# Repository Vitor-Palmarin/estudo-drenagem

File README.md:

# Automação de bancada experimental para determinação de percolação de água em minério de ferro

O grande fluxo de mercadorias ao redor do mundo é algo vital para a economia mundial, e com isso se faz necessário um transporte que possibilite uma grande movimentação de carga e com um bom custo-benefício. As malhas ferroviárias são uma ótima opção para fazer o transporte de cargas de grande porte, como grãos, minérios, entre outros, permitindo assim, uma conexão direta entre vários pontos de produção, desde a extração da obra-prima até a exportação do produto nos portos. O transporte de minérios é feito em vagões abertos, causando um acúmulo de água desnecessária sobre o material em épocas de chuva, e a fim de solucionar essa problemática, está sendo estudado o uso de drenos para fazer o escoamento de água livre. O uso de drenos para fazer o escoamento de água livre sofre constantes entupimentos, necessitando de paradas no transporte onerosas para sua desobstrução. 
Foi desenvolvido um protótipo de bancada experimental para o estudo do sistema de drenagem em amostras do minério de ferro do tipo Sinter feed com diferentes concentrações mássicas, utilizando uma bancada experimental desenvolvida com drenos confeccionados em ABS por uma impressora 3D. 

A automação da bancada utilizou um microcontrolador ATmega, que por meio de sensores de ultrassom foi medida a altura do fluído e armazenada os resultados da medição em um arquivo de extensão CSV por meio de um cartão Micro SD, durante um intervalo definido previamente definido, com exibição da coleta em tempo real em um display LCD.

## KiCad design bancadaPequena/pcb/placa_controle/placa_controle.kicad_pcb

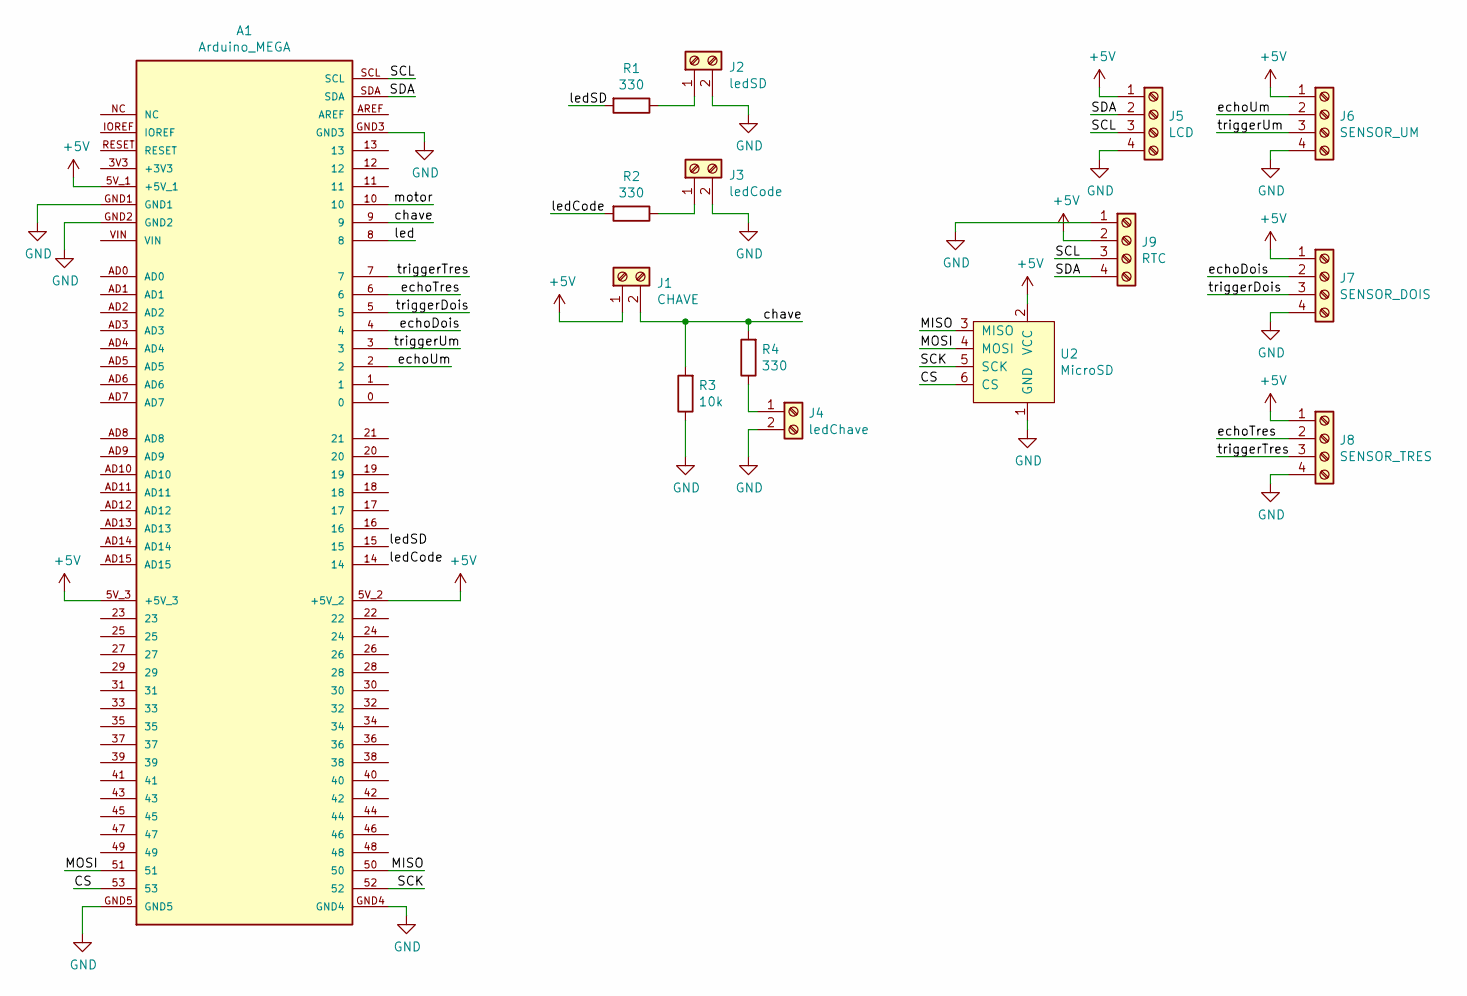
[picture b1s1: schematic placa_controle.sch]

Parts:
A1: Arduino_MEGA
J1: CHAVE; Altech_AK300_1x02_P5.00mm_45-Degree
J2: ledSD; PinSocket_1x02_P2.54mm_Vertical
J3: ledCode; PinSocket_1x02_P2.54mm_Vertical
J4: ledChave; PinSocket_1x02_P2.54mm_Vertical
J5: LCD; Altech_AK300_1x04_P5.00mm_45-Degree
J6: SENSOR_UM; Altech_AK300_1x04_P5.00mm_45-Degree
J7: SENSOR_DOIS; Altech_AK300_1x04_P5.00mm_45-Degree
J8: SENSOR_TRES; Altech_AK300_1x04_P5.00mm_45-Degree
J9: RTC; PinSocket_1x04_P2.54mm_Vertical
R1, R2, R4: 330; R_Axial_DIN0207_L6.3mm_D2.5mm_P10.16mm_Horizontal
R3: 10k; R_Axial_DIN0207_L6.3mm_D2.5mm_P10.16mm_Horizontal
U2: MicroSD; PinSocket_1x06_P2.54mm_Vertical

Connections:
+5V: A1.5V_1 (+5V_1), A1.5V_2 (+5V_2), A1.5V_3 (+5V_3), J1.1, J5.1, J6.1, J7.1, J8.1, J9.2, U2.2 (VCC)
/CS: A1.53, U2.6 (CS)
/MISO: A1.50, U2.3 (MISO)
/MOSI: A1.51, U2.4 (MOSI)
/SCK: A1.52, U2.5 (SCK)
/SCL: A1.SCL, J5.3, J9.3
/SDA: A1.SDA, J5.2, J9.4
/chave: A1.9, J1.2, R3.2, R4.2
/echoDois: A1.4, J7.2
/echoTres: A1.6, J8.2
/echoUm: A1.2, J6.2
/led: A1.8
/ledCode: A1.14, R2.2
/ledSD: A1.15, R1.2
/motor: A1.10
/triggerDois: A1.5, J7.3
/triggerTres: A1.7, J8.3
/triggerUm: A1.3, J6.3
GND: A1.GND1, A1.GND2, A1.GND3, A1.GND4, A1.GND5, J2.2, J3.2, J4.2, J5.4, J6.4, J7.4, J8.4, J9.1, R3.1, U2.1 (GND)
unnamed: J2.1, R1.1
unnamed: J3.1, R2.1
unnamed: J4.1, R4.1

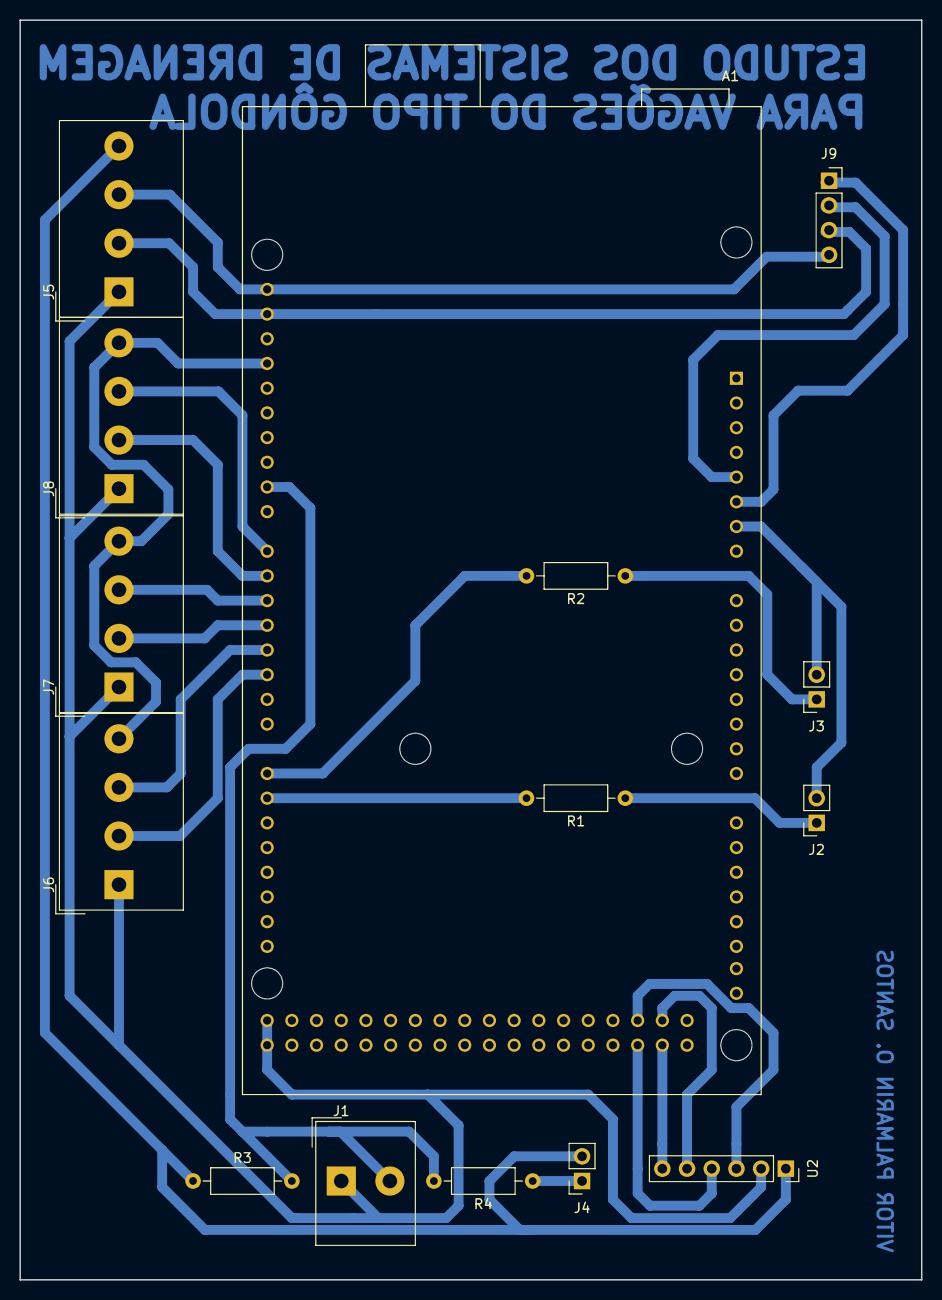
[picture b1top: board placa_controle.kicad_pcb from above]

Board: 2 copper layers, 92.7 x 129.5 mm, 15 parts (0 on the bottom side), 20 nets.

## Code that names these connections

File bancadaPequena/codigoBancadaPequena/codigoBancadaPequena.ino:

/* BANCADA EXPERIMENTAL PARA ESTUDO DOS SISTEMAS DE DRENAGEM PARA VAGÕES DE CARGA TIPO GÔNDOLA
 * 
 * DESENVOLVIDO POR: VITOR PALMARIN OLIVEIRA SANTOS - 10/2021
 * 
 */
// === DECLARACAO DE BIBLIOTECAS ===
#include <SPI.h>
#include <SD.h>
#include <Wire.h>;
#include <LiquidCrystal_I2C.h>;

// === DECLARAÇÃO DE OBJETOS ===
LiquidCrystal_I2C lcd(0x27, 20, 4);

// === PINAGEM ===
const int chipSelect = 10;

const int triggerUm = 2;
const int echoUm = 3;

const int triggerDois = 4;
const int echoDois = 5;

const int triggerTres = 6;
const int echoTres = 7;

const int led = 9;

const int chave = 8;

// === VARIAVEIS ===
long intervaloColeta = millis();
long intervaloLed = millis();
long intervaloExibicao = millis();

long pulsoUm, 
     pulsoDois, 
     pulsoTres;

int nivelUm, 
    nivelDois, 
    nivelTres;

const int alturaTanque = 506; // altura do tanque em milimetros

bool opcao = 0;

void setup()
{
  Serial.begin(9600);
  lcd.init();
  lcd.backlight();

  pinMode(triggerUm, OUTPUT);
  pinMode(echoUm, INPUT); 
  pinMode(triggerDois, OUTPUT);
  pinMode(echoDois, INPUT);
  pinMode(triggerTres, OUTPUT);
  pinMode(echoTres, INPUT);
  pinMode(led, OUTPUT);
  pinMode(chave, INPUT);

  digitalWrite(triggerUm, LOW);
  digitalWrite(triggerDois, LOW);
  digitalWrite(triggerTres, LOW);
  digitalWrite(led, LOW);
  
  Serial.println("Inicializando cartao SD...");
  if (!SD.begin(chipSelect))
  {
    Serial.println("Falha ao acessar o cartao !");
    Serial.println("Verifique o cartao/conexoes e reinicie o Arduino...");
    return;
  }
  Serial.println("Cartao iniciado corretamente !\n");
}

void loop()
{
  if((millis() - intervaloLed) >= 500){    // pisca o led no intervalo de 0,5 segundo
    intervaloLed = millis();
    digitalWrite(led,!digitalRead(led));
  }

  if((millis() - intervaloExibicao) >= 1000){   // exibe os dados no Serial a cada 1 segundo
    intervaloExibicao = millis();
    
    nivelUm = getDistancia(triggerUm, echoUm);
    nivelDois = getDistancia(triggerDois, echoDois);
    nivelTres = getDistancia(triggerTres, echoTres);

    exibeLCD();
    exibeSerial();
  }
  
  if((millis() - intervaloColeta) >= 60000){ // faz a coleta de dados a cada 1 minuto
    intervaloColeta = millis();
    if(digitalRead(chave)){
      saveData();                           // armazena os dados coletados na planilha
    }
  }
}

void exibeLCD(){
  lcd.clear();   
  lcd.setCursor(0,0);
  lcd.print("TEMPO = ");
  lcd.setCursor(8,0);
  lcd.print(millis()/1000);
  
  lcd.setCursor(0,1);
  lcd.print("SENSOR 1 = ");
  lcd.setCursor(11,1);
  lcd.print(nivelUm);
  
  lcd.setCursor(0,2);
  lcd.print("SENSOR 2 = ");
  lcd.setCursor(11,2);
  lcd.print(nivelDois);
  
  lcd.setCursor(0,3);
  lcd.print("SENSOR 3 = ");
  lcd.setCursor(11,3);
  lcd.print(nivelTres);
}

void exibeSerial(){
  Serial.println();
  Serial.print("TEMPO = ");
  Serial.print(millis()/1000);
  Serial.print(" s = ");
  Serial.print(millis()/60000);
  Serial.println(" min");
  Serial.println();
  
  // SENSOR 1
  Serial.print("Sensor 1 = ");
  Serial.print(nivelUm);
  Serial.println(" mm ");
  // SENSOR 2
  Serial.print("Sensor 2 = ");
  Serial.print(nivelDois);
  Serial.println(" mm ");
  
  // SENSOR 3
  Serial.print("Sensor 3 = ");
  Serial.print(nivelTres);
  Serial.println(" mm ");
  
  Serial.println();
}

long getDistancia(int trigger, int echo) {
    digitalWrite(trigger, HIGH);
    delayMicroseconds(5);
    digitalWrite(trigger, LOW);
    long pulso = pulseIn(echo, HIGH);
    long distanciaSensor = pulso / 2.9 / 2;
    if(opcao == 1) {        // opcao 1 = retorna o nivel do tanque a partir do fundo
      return alturaTanque - distanciaSensor;
    }
    else {                  // opcao 0 = retorna o nivel do tanque a partir do sensor
      return distanciaSensor;
    }
}

void saveData(){
  String fileName = "/datalog.csv";
  if(!SD.exists(fileName)){
    File file = SD.open(fileName, FILE_WRITE);
    if(!file){
      Serial.println("Failed to open file for writing");
      return;
    }
    if(file.println("ESTUDO DE DRENAGEM PARA VAGOES DE CARGA TIPO GONDOLA - UNISANTA")){
      Serial.println("File written");
    } else {
      Serial.println("Write failed");
    }
    if(file.println("DATA;HORA;TEMPO;SENSOR 1 [mm];SENSOR 2 [mm];SENSOR 3 [mm]")){
      Serial.println("Message appended");
    } else {
      Serial.println("Append failed");
    }
    if(file.println(";;" + String(millis()/60000) + ";" + String(nivelUm) + ";" + String(nivelDois) + ";" + String(nivelTres))){
      Serial.println("Message appended");
    } else {
      Serial.println("Append failed");
    }
    file.close();
  }
  else{
    File file = SD.open(fileName, FILE_WRITE);
    if(!file){
      Serial.println("Failed to open file for appending");
      return;
    }
    if(file.println(";;" + String(millis()/60000) + ";" + String(nivelUm) + ";" + String(nivelDois) + ";" + String(nivelTres))){
      Serial.println("Message appended");
    } else {
      Serial.println("Append failed");
    }
    file.close();
  }
}
